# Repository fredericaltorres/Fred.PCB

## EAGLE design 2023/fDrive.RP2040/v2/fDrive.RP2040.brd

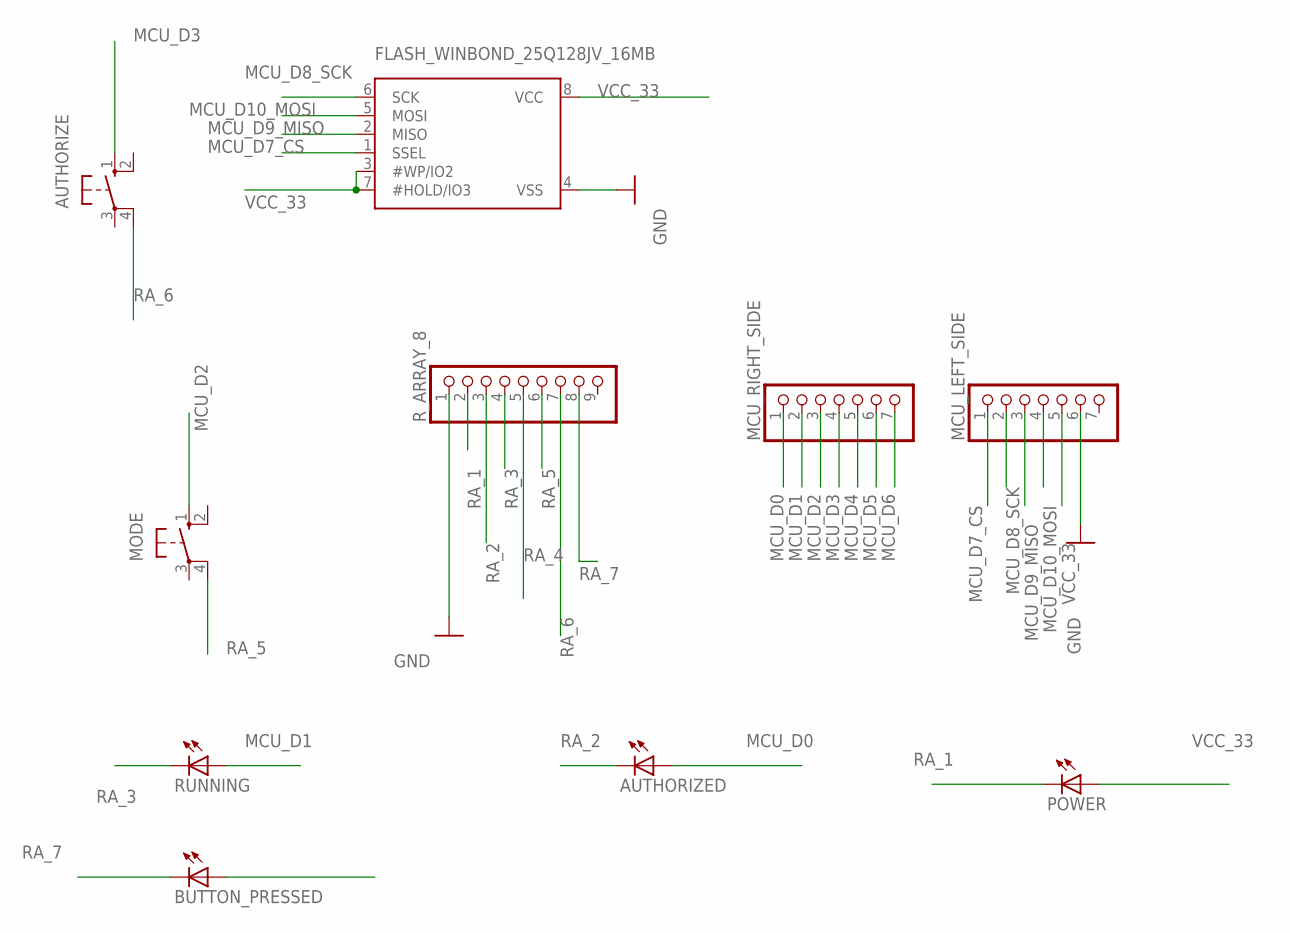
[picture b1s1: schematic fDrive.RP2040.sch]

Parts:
AUTHORIZE: 10-XX; B3F-10XX
AUTHORIZED: LEDSMT1206; 1206
BUTTON_PRESSED: LEDSMT1206; 1206
FLASH_WINBOND_25Q128JV_16MB: SPIFLASH_SOIC8208MIL; SOIC8_208MIL
MCU_LEFT_SIDE: PINHD-1X7; 1X07
MCU_RIGHT_SIDE: PINHD-1X7; 1X07
MODE: 10-XX; B3F-10XX
POWER: LEDSMT1206; 1206
RUNNING: LEDSMT1206; 1206
R_ARRAY_8: PINHD-1X9; 1X09-BIG

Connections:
GND: FLASH_WINBOND_25Q128JV_16MB.4 (VSS), MCU_LEFT_SIDE.6, R_ARRAY_8.1
MCU_D0: AUTHORIZED.A, MCU_RIGHT_SIDE.1
MCU_D1: MCU_RIGHT_SIDE.2, RUNNING.A
MCU_D2: MCU_RIGHT_SIDE.3, MODE.1 (S)
MCU_D3: AUTHORIZE.1 (S), MCU_RIGHT_SIDE.4
MCU_D4: BUTTON_PRESSED.A, MCU_RIGHT_SIDE.5
MCU_D5: MCU_RIGHT_SIDE.6
MCU_D6: MCU_RIGHT_SIDE.7
MCU_D7_CS: FLASH_WINBOND_25Q128JV_16MB.1 (SSEL), MCU_LEFT_SIDE.1
MCU_D8_SCK: FLASH_WINBOND_25Q128JV_16MB.6 (SCK), MCU_LEFT_SIDE.2
MCU_D9_MISO: FLASH_WINBOND_25Q128JV_16MB.2 (MISO), MCU_LEFT_SIDE.3
MCU_D10_MOSI: FLASH_WINBOND_25Q128JV_16MB.5 (MOSI), MCU_LEFT_SIDE.4
RA_1: POWER.C, R_ARRAY_8.2
RA_2: AUTHORIZED.C, R_ARRAY_8.3
RA_3: RUNNING.C, R_ARRAY_8.4
RA_4: R_ARRAY_8.5
RA_5: MODE.4 (P1), R_ARRAY_8.6
RA_6: AUTHORIZE.4 (P1), R_ARRAY_8.7
RA_7: BUTTON_PRESSED.C, R_ARRAY_8.8
VCC_33: FLASH_WINBOND_25Q128JV_16MB.3 (#WP/IO2), FLASH_WINBOND_25Q128JV_16MB.7 (#HOLD/IO3), FLASH_WINBOND_25Q128JV_16MB.8 (VCC), MCU_LEFT_SIDE.5, POWER.A

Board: 2 copper layers, 10 parts (0 on the bottom side), 17 nets, no tracks yet.

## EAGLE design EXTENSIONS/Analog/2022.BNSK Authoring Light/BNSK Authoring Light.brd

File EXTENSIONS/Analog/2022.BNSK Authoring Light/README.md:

g f G a b            4017B Pin
                       
                        _____
    a               f 5|1   16|Vcc  
    _               b 1|2   15|Rst
f  | | b            a 0|3   14|Clk
    -g              c 2|4   13|Clk I 
 e | | c            g 6|5   12|Cry 
    -             Rst 7|6   11|9
    d               d 3|7   10|4 e
                      G|8    9|8
e d G c dp              _____ 

Animation 

C:\DVT\Fred.PCB\EXTENSIONS\Analog\2022.BNSK Authoring Light

    RED WHITE BLUE
-----------------------    
A    x
B         x
C               x
D         x     x
E    x    x     x  
F    x    x  

A -> RED
B -> WHITE
C -> BLUE
D -> WHITE BLUE
E -> RED WHITE BLUE
F -> RED WHITE

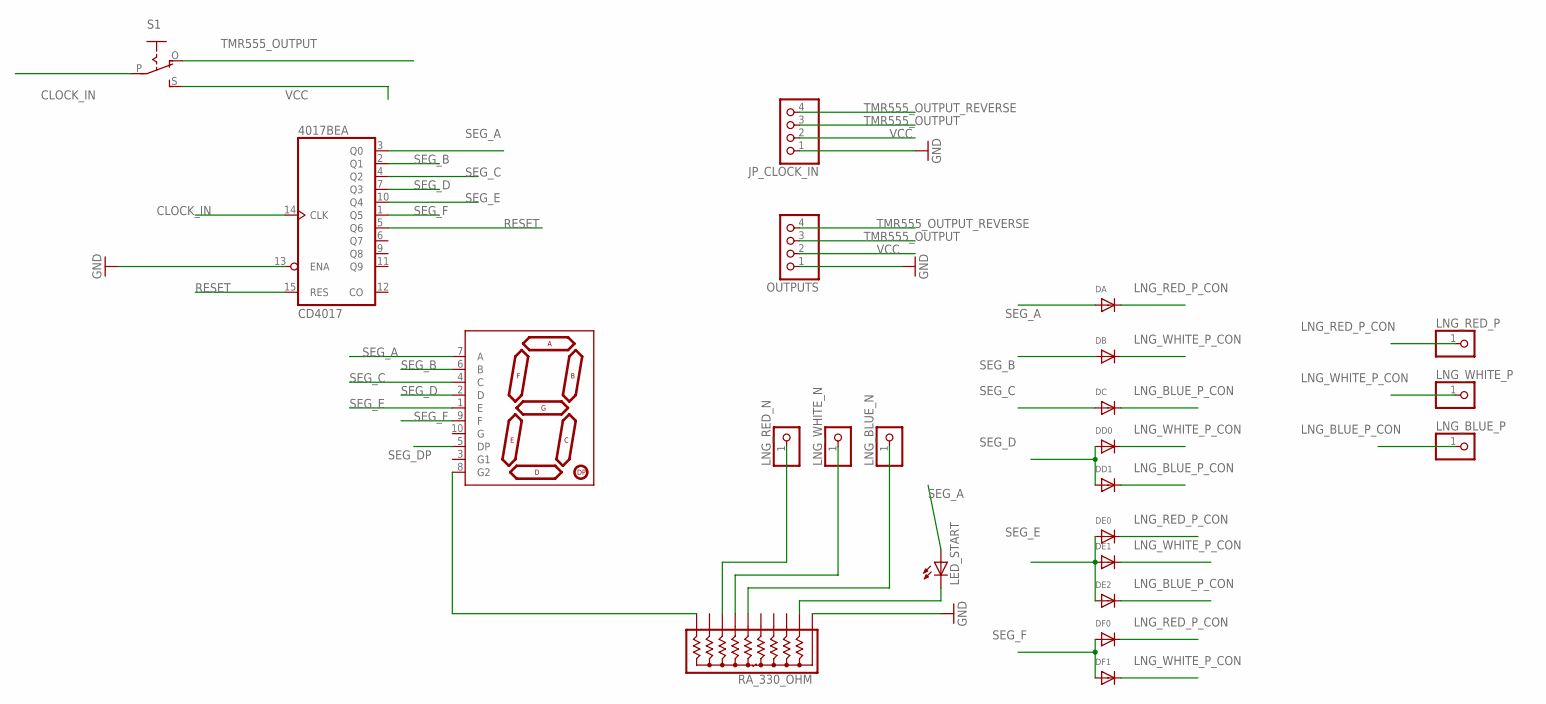
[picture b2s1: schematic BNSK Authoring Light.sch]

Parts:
4017BE: CD4017; DIL16
DA: DIODESMA; SMADIODE
DB: DIODESMA; SMADIODE
DC: DIODESMA; SMADIODE
DD0, DD1: DIODESMA; SMADIODE
DE0, DE1, DE2: DIODESMA; SMADIODE
DF0, DF1: DIODESMA; SMADIODE
JP_CLOCK_IN: PINHD-1X4; 1X04
LED_START: LEDSMT1206; 1206
LNG_BLUE_N: PINHD-1X1; 1X01
LNG_BLUE_P: PINHD-1X1; 1X01
LNG_RED_N: PINHD-1X1; 1X01
LNG_RED_P: PINHD-1X1; 1X01
LNG_WHITE_N: PINHD-1X1; 1X01
LNG_WHITE_P: PINHD-1X1; 1X01
OUTPUTS: PINHD-1X4; 1X04
RA_330_OHM: 4610X; SIP10
S1: EG1218S; EG1218
U$1: 7-SEGMENT-DISPLAYPTH; 7-SEGMENT-DISPLAY

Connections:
CLOCK_IN: 4017BE.14 (CLK), S1.P
GND: 4017BE.8 (GND), 4017BE.13 (ENA), JP_CLOCK_IN.1, OUTPUTS.1, RA_330_OHM.1
LNG_BLUE_P_CON: DC.C, DD1.C, DE2.C, LNG_BLUE_P.1
LNG_RED_P_CON: DA.C, DE0.C, DF0.C, LNG_RED_P.1
LNG_WHITE_P_CON: DB.C, DD0.C, DE1.C, DF1.C, LNG_WHITE_P.1
unnamed: LED_START.C, RA_330_OHM.2
unnamed: RA_330_OHM.10, U$1.8 (G2)
unnamed: LNG_RED_N.1, RA_330_OHM.8
unnamed: LNG_WHITE_N.1, RA_330_OHM.7
unnamed: LNG_BLUE_N.1, RA_330_OHM.6
RESET: 4017BE.5 (Q6), 4017BE.15 (RES)
SEG_A: 4017BE.3 (Q0), DA.A, LED_START.A, U$1.7 (A)
SEG_B: 4017BE.2 (Q1), DB.A, U$1.6 (B)
SEG_C: 4017BE.4 (Q2), DC.A, U$1.4 (C)
SEG_D: 4017BE.7 (Q3), DD0.A, DD1.A, U$1.2 (D)
SEG_DP: U$1.5 (DP)
SEG_E: 4017BE.10 (Q4), DE0.A, DE1.A, DE2.A, U$1.1 (E)
SEG_F: 4017BE.1 (Q5), DF0.A, DF1.A, U$1.9 (F)
TMR555_OUTPUT: JP_CLOCK_IN.3, OUTPUTS.3, S1.O
TMR555_OUTPUT_REVERSE: JP_CLOCK_IN.4, OUTPUTS.4
VCC: 4017BE.16 (VCC), JP_CLOCK_IN.2, OUTPUTS.2, S1.S

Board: 2 copper layers, 23 parts (0 on the bottom side), 20 nets, no tracks yet.

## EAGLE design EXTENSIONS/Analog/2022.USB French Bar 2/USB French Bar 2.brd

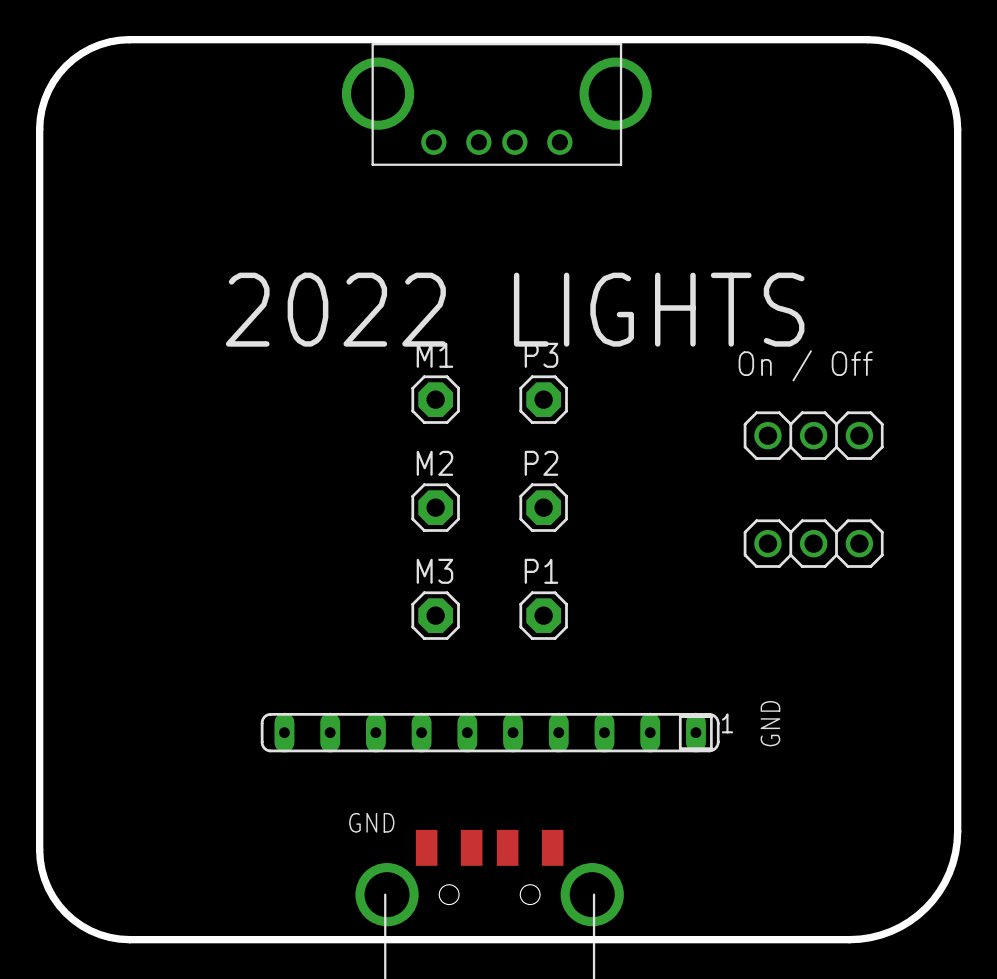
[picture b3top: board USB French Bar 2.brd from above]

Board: 2 copper layers, 51.0 x 50.0 mm, 11 parts (0 on the bottom side), 8 nets, no tracks yet.

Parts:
JP1, JP3: 1X03
M1, M2, M3: 1X01
P1, P2, P3: 1X01
RN1: SIP10
U$1: USB; USB-FEMALE-A-PTH
X1: USB-A; MOLEX_480371000

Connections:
unnamed: RN1.1, U$1.GND, X1.4
unnamed: M1.1, RN1.10
unnamed: U$1.D+, X1.3
unnamed: U$1.D-, X1.2
unnamed: M2.1, RN1.8
unnamed: M3.1, RN1.4
unnamed: JP1.2, P1.1, P2.1, P3.1
VCC: JP1.1, U$1.VBUS, X1.1

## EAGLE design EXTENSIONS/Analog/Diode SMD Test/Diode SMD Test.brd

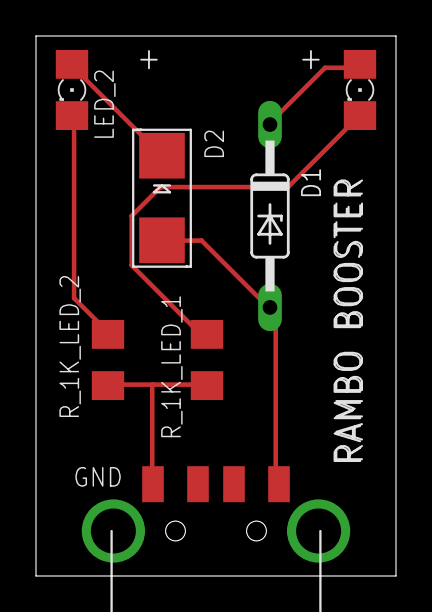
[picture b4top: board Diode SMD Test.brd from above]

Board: 2 copper layers, 20.0 x 30.0 mm, 7 parts (0 on the bottom side), 6 nets.

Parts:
D1: 1N821; DO35Z10
D2: SMADIODE
LED_1, LED_2: 1206
R_1K_LED_1, R_1K_LED_2: R1206
X1: USB-A; MOLEX_480371000

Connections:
GND: R_1K_LED_1.1, R_1K_LED_2.1, X1.4
LED_1: LED_1.C, R_1K_LED_1.2
unnamed: D1.C, LED_1.A
unnamed: LED_2.C, R_1K_LED_2.2
unnamed: D2.C, LED_2.A
VCC: D1.A, D2.A, X1.1

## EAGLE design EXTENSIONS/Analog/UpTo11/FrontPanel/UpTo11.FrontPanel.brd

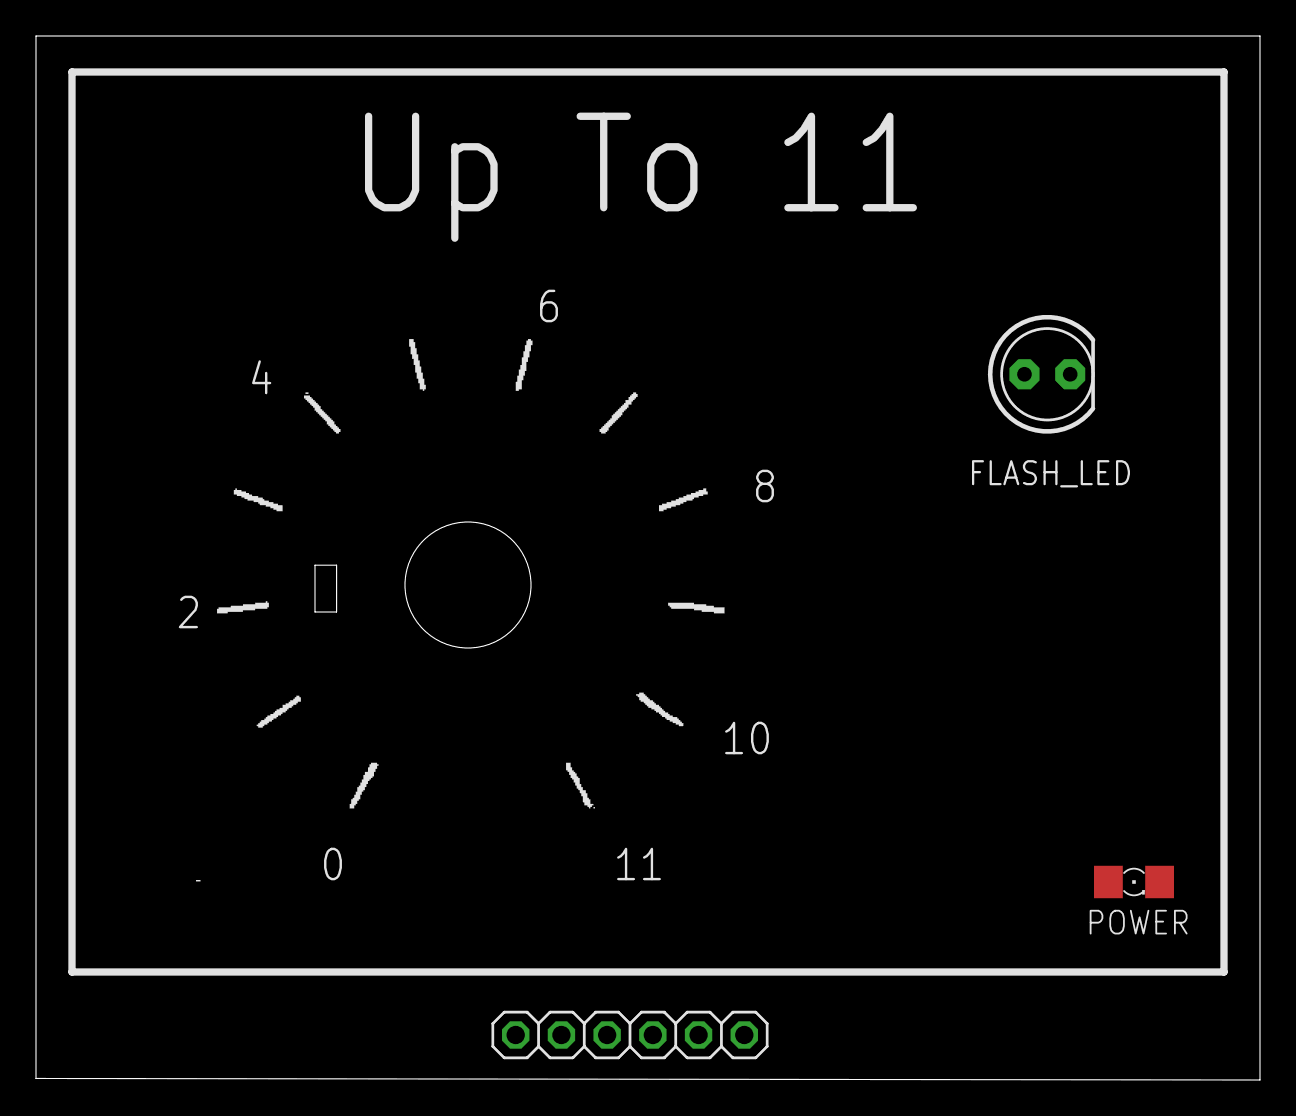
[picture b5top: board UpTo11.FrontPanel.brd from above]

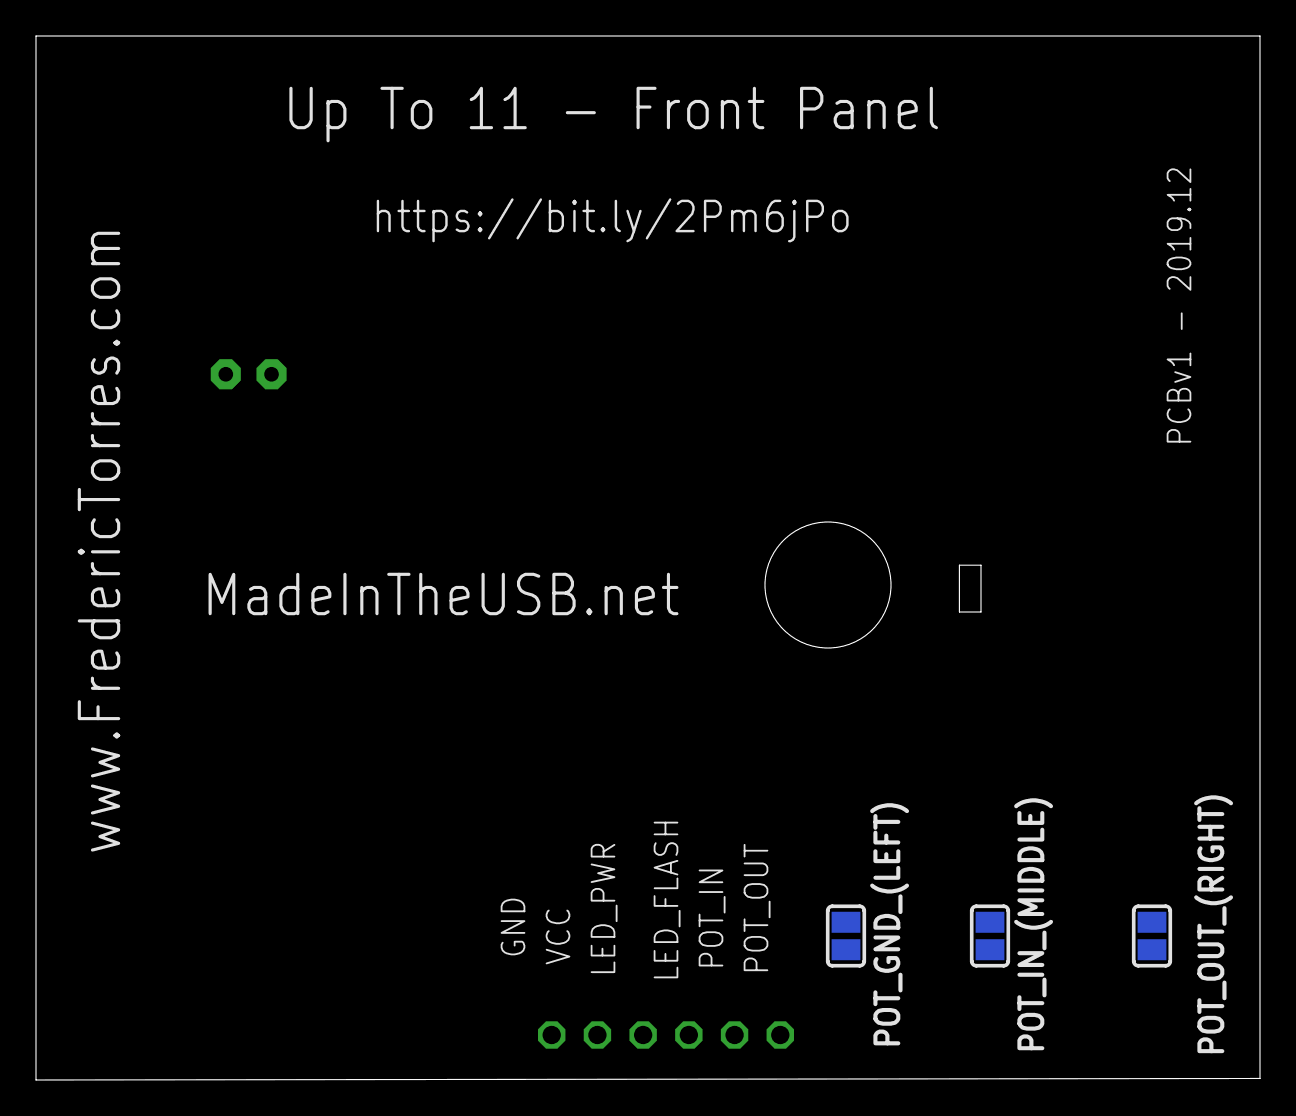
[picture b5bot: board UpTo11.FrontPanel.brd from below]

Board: 2 copper layers, 68.0 x 58.0 mm, 6 parts (3 on the bottom side), 5 nets, no tracks yet.

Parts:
FLASH_LED: LED5MM
FRONT_PANEL_INTERFACE: 1X06
POT_GND_(LEFT): SOLDERJUMPER_REFLOW
POT_IN_(MIDDLE): SOLDERJUMPER_REFLOW
POT_OUT_(RIGHT): SOLDERJUMPER_REFLOW
POWER: 1206

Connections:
GND_EX: FLASH_LED.K, FRONT_PANEL_INTERFACE.1, POT_GND_(LEFT).2, POWER.C
LED_FLASH: FLASH_LED.A, FRONT_PANEL_INTERFACE.4
LED_PWR: FRONT_PANEL_INTERFACE.3, POWER.A
POT_IN: FRONT_PANEL_INTERFACE.5, POT_IN_(MIDDLE).2
POT_OUT: FRONT_PANEL_INTERFACE.6, POT_OUT_(RIGHT).2

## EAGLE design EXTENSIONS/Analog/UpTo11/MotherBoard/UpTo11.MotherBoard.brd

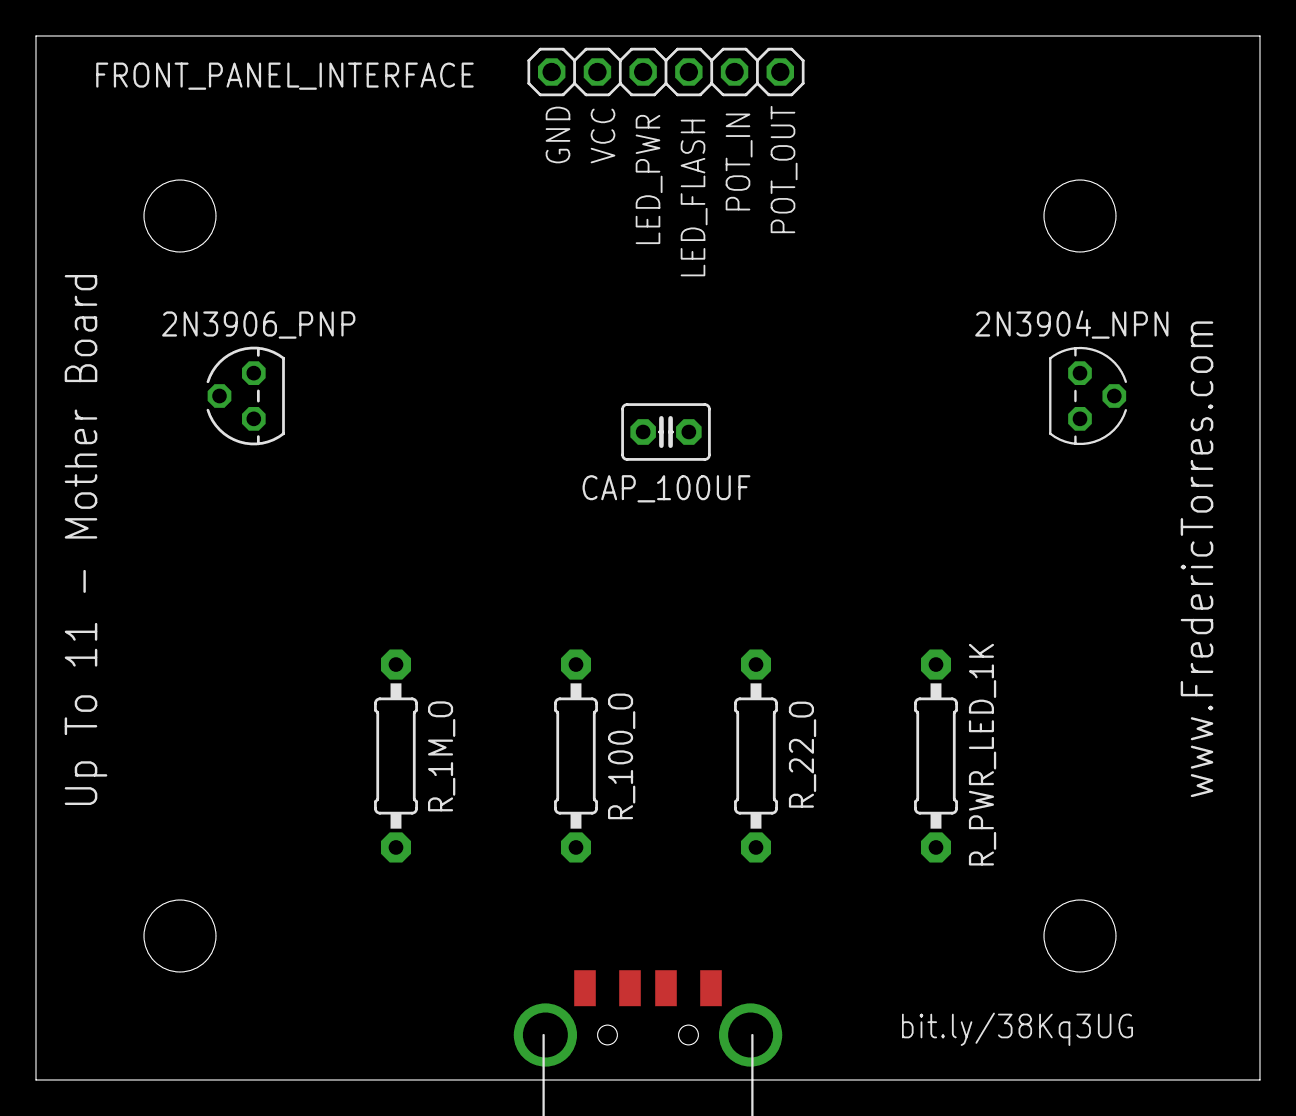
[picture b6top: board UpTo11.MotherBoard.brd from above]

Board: 2 copper layers, 68.0 x 58.0 mm, 9 parts (0 on the bottom side), 9 nets, no tracks yet.

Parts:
2N3904_NPN: 2N3904; TO92
2N3906_PNP: 2N3906; TO92
CAP_100UF: C025-030X050
FRONT_PANEL_INTERFACE: 1X06
R_1M_O, R_22_O, R_100_O: 0207/10
R_PWR_LED_1K: 0207/10
X1: USB-A; MOLEX_480371000

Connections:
GND_EX: FRONT_PANEL_INTERFACE.1, R_1M_O.1, X1.4
LED_FLASH: 2N3904_NPN.3, FRONT_PANEL_INTERFACE.4
LED_PWR: FRONT_PANEL_INTERFACE.3, R_PWR_LED_1K.1
unnamed: 2N3904_NPN.1, CAP_100UF.2, R_22_O.1
unnamed: 2N3906_PNP.2, CAP_100UF.1, R_1M_O.2
unnamed: 2N3906_PNP.1, R_100_O.1
POT_IN: FRONT_PANEL_INTERFACE.5, R_100_O.2
POT_OUT: 2N3904_NPN.2, FRONT_PANEL_INTERFACE.6
VCC: 2N3906_PNP.3, FRONT_PANEL_INTERFACE.2, R_22_O.2, R_PWR_LED_1K.2, X1.1

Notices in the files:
parts and their libraries:
microbuilder: This work is placed in the public domain, and may be freely used for commercial and non-commercial work with the following conditions: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
SparkFun-DigitalIC: Licensing: Creative Commons ShareAlike 4.0 International - https://creativecommons.org/licenses/by-sa/4.0
